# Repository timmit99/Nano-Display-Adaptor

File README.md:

# RepRap-Display-Controller
Arduino Nano compatable board to controll a RepRap display

This board maps an arduino nano's pins onto the 2 2x5 pin IDC cables needed for a RepRapDiscount Smart Controller or RepRapDiscount Full Graphic Smart Controller.

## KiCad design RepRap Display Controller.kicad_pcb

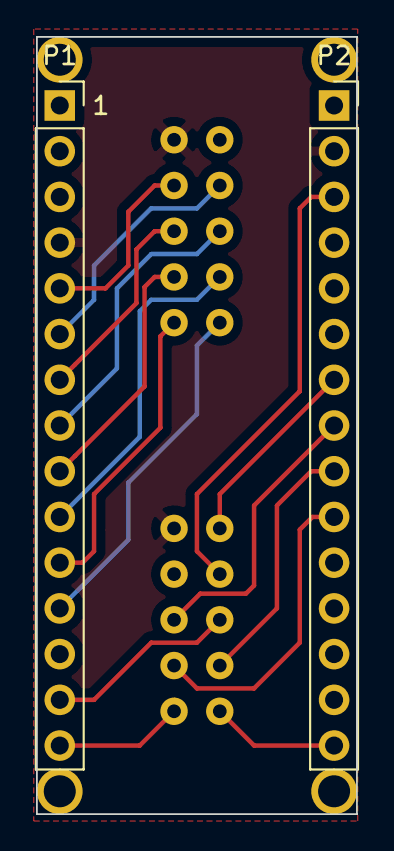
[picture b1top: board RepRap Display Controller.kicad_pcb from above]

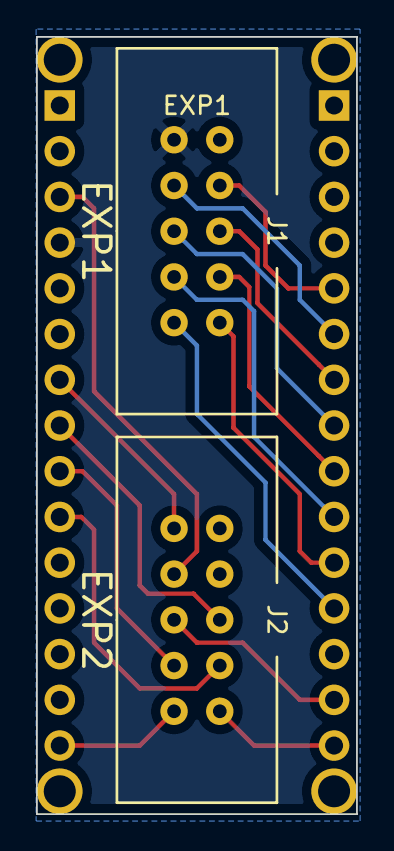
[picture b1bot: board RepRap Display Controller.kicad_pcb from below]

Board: 2 copper layers, 17.8 x 43.2 mm, 8 parts (2 on the bottom side), 18 nets.

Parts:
J1: EXP1; Shrouded_2x5_pin_header
J2: EXP2; Shrouded_2x5_pin_header
P1: Digital; PinSocket_1x15_P2.54mm_Vertical
P2: Analog; PinSocket_1x15_P2.54mm_Vertical
P3, P4, P5, P6: CONN_01X01; 1pin_Nano

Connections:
+5V: J1.10, P2.4
/2: J1.7, P1.5
/3(**): J1.8, P1.6
/4: J1.5, P1.7
/5(**): J1.6, P1.8
/6(**): J1.3, P1.9
/7: J1.4, P1.10
/8: J1.1, P1.11
/9(**): J1.2, P1.12
/11(**/MOSI): J2.6, P1.14
/12(MISO): J2.1, P1.15
/13(SCK): J2.2, P2.15
/A2: J2.3, P2.10
/A3: J2.4, P2.9
/A4: J2.5, P2.8
/A5: J2.10, P2.7
/Reset: J2.8, P2.3
GND: J1.9, J2.9, P1.4, P2.2

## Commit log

2019-10-18 Initial Commit
    Board designed to interface an Ardunio Nano to a repara 12864 display or the 2016 displays using 2 x 10 pin IDC cables
2019-10-18 Reorganization and Klipper Config
    Files organized into folders for ease of navigation. Also added an UNTESTED Klipper .cfg file that can be included into the main printer.cfg to enable this disaply adaptor.
2019-10-26 Update NanoDisplay.cfg
    Changing pin names to work properly=P
2020-02-12 Added license and versioning to PCB
    Added V1.0 to board for proper versioning going forward and CC BY-NC license.
    Basically, Full reign to share and modify as long as it is NOT used commercial and retains all attribution to the source.
2020-02-12 Gerber Update for V1.0
    Pushed updated gerbers for V1.0
2020-02-12 Project Zip
